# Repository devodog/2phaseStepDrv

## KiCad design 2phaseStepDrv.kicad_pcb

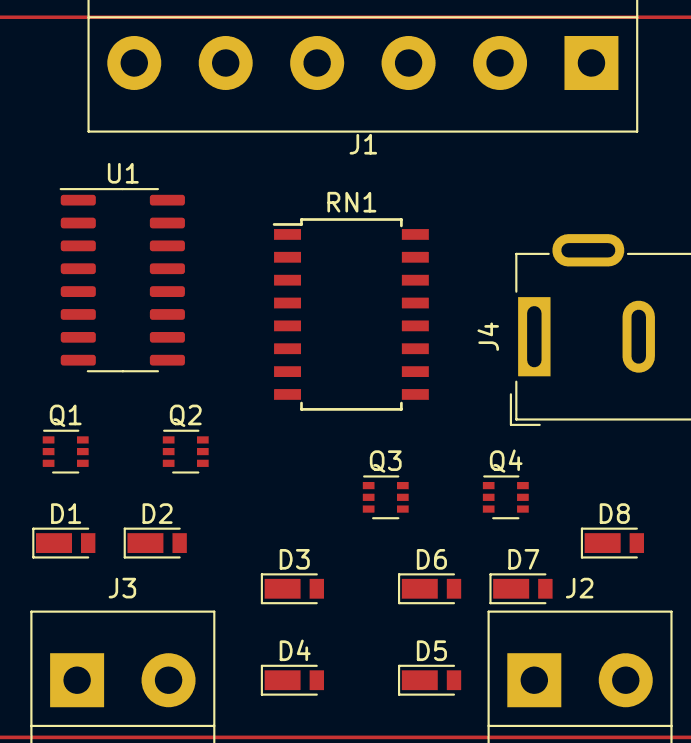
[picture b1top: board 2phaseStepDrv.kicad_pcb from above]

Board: 2 copper layers, 18 parts (0 on the bottom side), 21 nets, no tracks yet.

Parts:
D1, D2, D3, D4, D5, D6, D7, D8: 1N4149; D_TUMD2
J1: Screw_Terminal_01x06; TerminalBlock_bornier-6_P5.08mm
J2, J3: Screw_Terminal_01x02; TerminalBlock_bornier-2_P5.08mm
J4: Jack-DC; BarrelJack_Wuerth_6941xx301002
Q1, Q2, Q3, Q4: MBT2222ADW1T1; SOT-363_SC-70-6
RN1: R_Pack08; SOIC-16W_5.3x10.2mm_P1.27mm
U1: 4028; SOIC-16_3.9x9.9mm_P1.27mm

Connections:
+12V: D1.1 (K), D3.1 (K), D5.1 (K), D7.1 (K), J1.5, J4.1, Q1.3 (C2), Q2.3 (C2), Q3.3 (C2), Q4.3 (C2), U1.16 (VDD)
Earth: D2.2 (A), D4.2 (A), D6.2 (A), D8.2 (A), J1.6, J4.2, Q1.1 (E1), Q2.1 (E1), Q3.1 (E1), Q4.1 (E1), U1.8 (VSS), U1.11 (D)
unnamed: D1.2 (A), D2.1 (K), J3.1, Q1.4 (E2), Q2.6 (C1)
unnamed: J1.1, U1.10 (A)
unnamed: J1.2, U1.13 (B)
unnamed: J1.3, U1.12 (C)
unnamed: D5.2 (A), D6.1 (K), J2.1, Q3.4 (E2), Q4.6 (C1)
unnamed: D7.2 (A), D8.1 (K), J2.2, Q3.6 (C1), Q4.4 (E2)
unnamed: D3.2 (A), D4.1 (K), J3.2, Q1.6 (C1), Q2.4 (E2)
unnamed: Q4.2 (B1), RN1.1 (R1.1)
unnamed: Q4.5 (B2), RN1.2 (R2.1)
unnamed: Q3.2 (B1), RN1.3 (R3.1)
unnamed: Q3.5 (B2), RN1.4 (R4.1)
unnamed: Q2.2 (B1), RN1.5 (R5.1)
unnamed: Q2.5 (B2), RN1.6 (R6.1)
unnamed: Q1.2 (B1), RN1.7 (R7.1)
unnamed: Q1.5 (B2), RN1.8 (R8.1)
unnamed: RN1.9 (R8.2), RN1.10 (R7.2), U1.3 (S0)
unnamed: RN1.11 (R6.2), RN1.12 (R5.2), U1.14 (S1)
unnamed: RN1.13 (R4.2), RN1.14 (R3.2), U1.2 (S2)
unnamed: RN1.15 (R2.2), RN1.16 (R1.2), U1.15 (S3)

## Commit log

2022-08-04 ver0
2022-08-05 Changed devices and included foot-prints
2022-08-07 new footprints and diodes
2022-08-11 Updated transistors, added flybacks and adjusted foor-prints
